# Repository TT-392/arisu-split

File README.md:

# Warning
For the actual arisu keyboard PCB go to https://github.com/FateNozomi/arisu-pcb, this one is just an unfinished fork.

# Arisu Keyboard PCB
アリス PCB designed using KiCad. The layout is inspired by Lyn's EM7 and TGR Alice with some modification of my own.

Key differences:
- I removed the extra [B] key on the right half and shifted the [NM,.?] row to the left by 0.25U.
- Shifted the 3 keys to the right and added arrow keys.
- Tweaked the bottom so that the 1.5U keys doesn't protrude out a little.

Shifting the [NM,.?] row to the left by 0.25U required quite some work on the arrangement of keys for the right half.
As a result, this does not give the same typing experience as Lyn's EM7 and TGR Alice.
Lyn's EM7 and TGR Alice uses the home row as the center point to vertically align both halves while I used the number row instead.
Due to the nature of staggered keyboards, aligning using the number row resulted in the home row not being aligned.

Disclaimer: Use these files at your own risk.

## Gerber Files
Download the gerber files under [releases](https://github.com/FateNozomi/arisu-pcb/releases).

## Assembly
For the components required, you may refer to the bill of materials included along with the release as reference or load up the design file in KiCad.
All the components can be soldered using a regular soldering iron, though soldering the Micro USB receptacle might be the biggest hurdle.

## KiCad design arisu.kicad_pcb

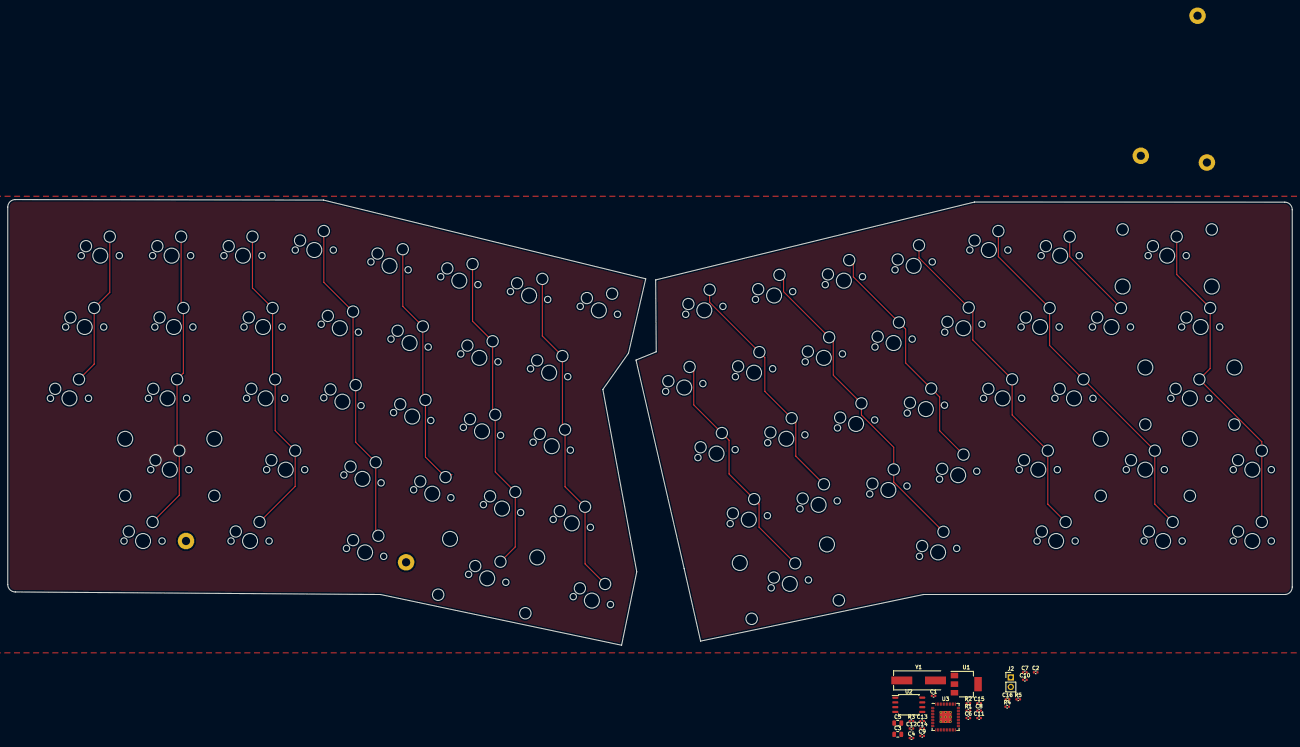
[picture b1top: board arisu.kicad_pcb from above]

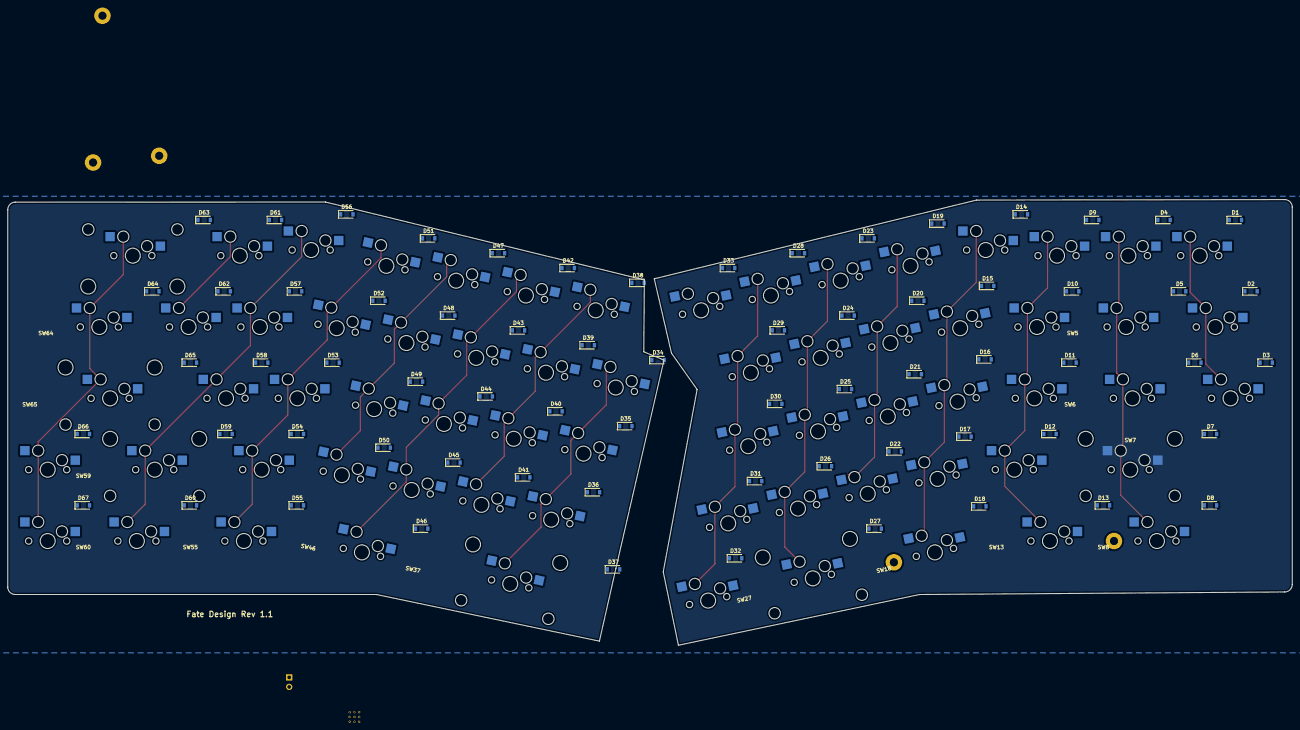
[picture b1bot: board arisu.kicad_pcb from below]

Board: 2 copper layers, 343.0 x 119.0 mm, 165 parts (67 on the bottom side), 108 nets.

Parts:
C1, C2: 27p; C_0402_1005Metric
C3, C5: 10u; C_0805_2012Metric
C4, C6, C7, C9, C11, C12, C13, C14, C15, C16: 100n; C_0402_1005Metric
C8, C10: 1u; C_0402_1005Metric
D1, D2, D3, D4, D5, D6, D7, D8, D9, D10, D11, D12, D13, D14, D15, D16, D17, D18, D19, D20, D21, D22, D23, D24, D25, D26, D27, D28, D29, D30, D31, D32, D33, D34, D35, D36, D37, D38, D39, D40, D41, D42, D43, D44, D45, D46, D47, D48, D49, D50, D51, D52, D53, D54, D55, D56, D57, D58, D59, D60, D61, D62, D63, D64, D65, D66, D67: D; D_SOD-123
H1, H2, H4, H6, H7: MountingHole; MountingHole_2.2mm_M2_Pad
J2: Conn_01x02; PinHeader_1x02_P2.54mm_Vertical
R1, R3: 1k; C_0402_1005Metric
R2: DNF; C_0402_1005Metric
R4, R5: 27; C_0402_1005Metric
SW1, SW2, SW3, SW4, SW9, SW10, SW11, SW12, SW14, SW15, SW16, SW17, SW19, SW20, SW21, SW22, SW23, SW24, SW25, SW26, SW28, SW29, SW30, SW31, SW32, SW33, SW34, SW35, SW36, SW38, SW39, SW40, SW41, SW42, SW43, SW44, SW45, SW47, SW48, SW49, SW50, SW51, SW52, SW53, SW54, SW56, SW57, SW58, SW61, SW62, SW66, SW67: SW_Push; SW_Cherry_MX_1.00u_PCB_Socket
SW5, SW8, SW13, SW18, SW46, SW55, SW60, SW64: SW_Push; SW_Cherry_MX_1.50u_PCB_Socket
SW6: SW_Push; SW_Cherry_MX_1.75u_PCB_Socket
SW7, SW65: SW_Push; SW_Cherry_MX_2.25u_PCB_Socket_ReversedStabilizers
SW27, SW59: SW_Push; SW_Cherry_MX_2.00u_PCB_Socket_ReversedStabilizers
SW37: SW_Push; SW_Cherry_MX_2.75u_PCB_Socket_ReversedStabilizers
SW63: SW_Push; SW_Cherry_MX_2.00u_PCB_Socket
U1: NCP1117-3.3_SOT223; SOT-223-3_TabPin2
U2: W25Q128JVS; SOIC-8_5.23x5.23mm_P1.27mm
U3: RP2040; RP2040-QFN-56
Y1: ABLS-12.000MHZ-B4-T; Crystal_SMD_HC49-US

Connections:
+3V3_L: C4.1, C5.1, C9.1, C10.1, C11.1, C12.1, C13.1, C14.1, C15.1, C16.1, R2.1, U1.2 (VO), U2.8 (VCC), U3.1 (IOVDD), U3.10 (IOVDD), U3.22 (IOVDD), U3.26 (RUN), U3.33 (IOVDD), U3.42 (IOVDD), U3.43 (ADC_AVDD), U3.44 (VREG_IN), U3.48 (USB_VDD), U3.49 (IOVDD)
+5R: C3.1, U1.3 (VI)
/Left/matrixL/col0: SW1.1, SW2.1, SW3.1
/Left/matrixL/col1: SW4.1, SW5.1, SW6.1, SW7.1, SW8.1
/Left/matrixL/col2: SW9.1, SW10.1, SW11.1, SW12.1, SW13.1
/Left/matrixL/col3: SW14.1, SW15.1, SW16.1, SW17.1, SW18.1
/Left/matrixL/col4: SW19.1, SW20.1, SW21.1, SW22.1, SW33.1
/Left/matrixL/col5: SW23.1, SW24.1, SW25.1, SW26.1, SW27.1
/Left/matrixL/col6: SW28.1, SW29.1, SW30.1, SW31.1, SW32.1
/Left/matrixL/row0: D1.1 (K), D4.1 (K), D9.1 (K), D14.1 (K), D19.1 (K), D23.1 (K), D28.1 (K)
/Left/matrixL/row1: D2.1 (K), D5.1 (K), D10.1 (K), D15.1 (K), D20.1 (K), D24.1 (K), D29.1 (K)
/Left/matrixL/row2: D3.1 (K), D6.1 (K), D11.1 (K), D16.1 (K), D21.1 (K), D25.1 (K), D30.1 (K)
/Left/matrixL/row3: D7.1 (K), D12.1 (K), D17.1 (K), D22.1 (K), D26.1 (K), D31.1 (K)
/Left/matrixL/row4: D8.1 (K), D13.1 (K), D18.1 (K), D27.1 (K), D32.1 (K), D33.1 (K)
/Right/1V1: C6.1, C7.1, C8.1, U3.23 (DVDD), U3.45 (VREG_VOUT), U3.50 (DVDD)
/Right/QSPI_SCLK: U2.6 (CLK), U3.52 (QSPI_SCLK)
/Right/QSPI_SD0: U2.5 (DI(IO0)), U3.53 (QSPI_SD0)
/Right/QSPI_SD1: U2.2 (DO(IO1)), U3.55 (QSPI_SD1)
/Right/QSPI_SD2: U2.3 (IO2), U3.54 (QSPI_SD2)
/Right/QSPI_SD3: U2.7 (IO3), U3.51 (QSPI_SD3)
/Right/QSPI_SS: R1.1, R2.2, U2.1 (~CS), U3.56 (QSPI_SS)
/Right/XIN: C1.1, U3.20 (XIN), Y1.1
/Right/XOUT: R3.1, U3.21 (XOUT)
/Right/matrixR/col0: SW34.1, SW35.1, SW36.1, SW37.1, U3.2 (GPIO0)
/Right/matrixR/col1: SW38.1, SW39.1, SW40.1, SW41.1, U3.3 (GPIO1)
/Right/matrixR/col2: SW42.1, SW43.1, SW44.1, SW45.1, SW46.1, U3.4 (GPIO2)
/Right/matrixR/col3: SW47.1, SW48.1, SW49.1, SW50.1, U3.5 (GPIO3)
/Right/matrixR/col4: SW51.1, SW52.1, SW53.1, SW54.1, SW55.1, U3.6 (GPIO4)
/Right/matrixR/col5: SW56.1, SW57.1, SW58.1, SW59.1, SW60.1, U3.7 (GPIO5)
/Right/matrixR/col6: SW61.1, SW62.1, U3.8 (GPIO6)
/Right/matrixR/col7: SW63.1, SW64.1, SW65.1, SW66.1, SW67.1, U3.9 (GPIO7)
/Right/matrixR/row0: D38.1 (K), D42.1 (K), D47.1 (K), D51.1 (K), D56.1 (K), D61.1 (K), D63.1 (K), U3.11 (GPIO8)
/Right/matrixR/row1: D34.1 (K), D39.1 (K), D43.1 (K), D48.1 (K), D52.1 (K), D57.1 (K), D62.1 (K), D64.1 (K), U3.12 (GPIO9)
/Right/matrixR/row2: D35.1 (K), D40.1 (K), D44.1 (K), D49.1 (K), D53.1 (K), D58.1 (K), D65.1 (K), U3.13 (GPIO10)
/Right/matrixR/row3: D36.1 (K), D41.1 (K), D45.1 (K), D50.1 (K), D54.1 (K), D59.1 (K), D66.1 (K), U3.14 (GPIO11)
/Right/matrixR/row4: D37.1 (K), D46.1 (K), D55.1 (K), D60.1 (K), D67.1 (K), U3.15 (GPIO12)
/Right/~USB_BOOT: J2.1, R1.2
GND: C1.2, C2.2, C3.2, C4.2, C5.2, C6.2, C7.2, C8.2, C9.2, C10.2, C11.2, C12.2, C13.2, C14.2, C15.2, C16.2, J2.2, U1.1 (GND), U2.4 (GND), U3.19 (TESTEN), U3.57 (GND)
unnamed: C2.1, R3.2, Y1.2
unnamed: D1.2 (A), SW1.2
unnamed: D2.2 (A), SW2.2
unnamed: D3.2 (A), SW3.2
unnamed: D4.2 (A), SW4.2
unnamed: D5.2 (A), SW5.2
unnamed: D6.2 (A), SW6.2
unnamed: D7.2 (A), SW7.2
unnamed: D8.2 (A), SW8.2
unnamed: D9.2 (A), SW9.2
unnamed: D10.2 (A), SW10.2
unnamed: D11.2 (A), SW11.2
unnamed: D12.2 (A), SW12.2
unnamed: D13.2 (A), SW13.2
unnamed: D14.2 (A), SW14.2
unnamed: D15.2 (A), SW15.2
unnamed: D16.2 (A), SW16.2
unnamed: D17.2 (A), SW17.2
unnamed: D18.2 (A), SW18.2
unnamed: D19.2 (A), SW19.2
unnamed: D20.2 (A), SW20.2
unnamed: D21.2 (A), SW21.2
unnamed: D22.2 (A), SW22.2
unnamed: D23.2 (A), SW23.2
unnamed: D24.2 (A), SW24.2
unnamed: D25.2 (A), SW25.2
unnamed: D26.2 (A), SW26.2
unnamed: D27.2 (A), SW27.2
unnamed: D28.2 (A), SW28.2
unnamed: D29.2 (A), SW29.2
unnamed: D30.2 (A), SW30.2
unnamed: D31.2 (A), SW31.2
unnamed: D32.2 (A), SW32.2
unnamed: D33.2 (A), SW33.2
unnamed: D34.2 (A), SW34.2
unnamed: D35.2 (A), SW35.2
unnamed: D36.2 (A), SW36.2
unnamed: D37.2 (A), SW37.2
unnamed: D38.2 (A), SW38.2
unnamed: D39.2 (A), SW39.2
unnamed: D40.2 (A), SW40.2
unnamed: D41.2 (A), SW41.2
unnamed: D42.2 (A), SW42.2
unnamed: D43.2 (A), SW43.2
unnamed: D44.2 (A), SW44.2
unnamed: D45.2 (A), SW45.2
unnamed: D46.2 (A), SW46.2
unnamed: D47.2 (A), SW47.2
unnamed: D48.2 (A), SW48.2
unnamed: D49.2 (A), SW49.2
unnamed: D50.2 (A), SW50.2
unnamed: D51.2 (A), SW51.2
unnamed: D52.2 (A), SW52.2
unnamed: D53.2 (A), SW53.2
unnamed: D54.2 (A), SW54.2
unnamed: D55.2 (A), SW55.2
unnamed: D56.2 (A), SW56.2
unnamed: D57.2 (A), SW57.2
unnamed: D58.2 (A), SW58.2
unnamed: D59.2 (A), SW59.2
unnamed: D60.2 (A), SW60.2
unnamed: D61.2 (A), SW61.2
unnamed: D62.2 (A), SW62.2
unnamed: D63.2 (A), SW63.2
unnamed: D64.2 (A), SW64.2
unnamed: D65.2 (A), SW65.2
unnamed: D66.2 (A), SW66.2
unnamed: D67.2 (A), SW67.2
unnamed: R4.2, U3.47 (USB_DP)
unnamed: R5.2, U3.46 (USB_DM)

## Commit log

2019-01-27 Move all footprints F.SilkS label to B.SilkS
2019-01-28 Add Buzzer_AST1109MLTRQ footprint
2019-01-28 Add Komi art footprint
2019-06-03 Organize parts
2019-06-04 Add HRO TYPE-C-31-M-12 footprint
2019-06-07 Add Kailh PCB Socket 1.00u and 2.00u footprint
2019-06-07 Add HRO TYPE-C-31-M-12 symbol library
2019-06-10 Define Kailh PCB Socket 1.00u and 2.00u courtyard
2019-07-25 Create LICENSE
2019-10-23 Add centered MX 1.00u, 2.00u, 6.25u and 7.00u footprints
2019-11-02 Remove Miscellaneous footprints
2019-11-02 Add SWD and I2C headers
2019-11-03 Add Fate logo
2020-10-20 Update .gitignore to include *.sch-bak
2020-10-20 Update symbol library to 5.1.7 USB_B_Micro USBLC6-25C6 ATmega32U4-AU
2020-10-20 Update MX_Switch footprints from Fate_Parts
2022-07-31 Convert to new kicad format
2022-07-31 Update 3d models
2022-07-31 Add Readme
2022-08-02 new layout
2022-08-03 scripting tests
2022-08-03 Added keycap models
2022-08-03 Convert stl files to step
2022-08-03 new commits in submodules
2022-08-03 Update remote of submodules
2022-08-04 Add RP2040
2022-08-04 Remove some more old files
2022-08-04 Split the keyboard into multiple files, give both sides a micro, and added 1 of the 2 jack circuits
2022-08-07 Hot pluggable trrs
2022-08-07 Added socketed versions of some keycaps, and center keycaps
2022-08-07 No more erc errors + centering and socketing of switches
2022-08-10 Add second micro back in, and added some footprints
2022-08-12 Schematic mostly finished
2022-08-12 Some layout
2022-08-17 Removed stabilizer holes from a footprint
2022-08-17 more layout, and some 3d files
2022-08-18 remove Fate_Parts submodule
2022-08-18 Remove the other 2 submodules
2022-08-20 Finished layout (for now), board outline, and new trrs jacks
2022-08-20 Moved some stuff´
2022-08-20 Moved footprints and 3d models into directories
2022-08-20 Move symbols into symbols folder
2022-08-22 Started work on e.eco case cutout
2022-08-24 Add cutout drawings
2022-10-17 plates added
2022-11-03 expand plate edges
2022-11-05 left side of keyboard finished for the time being
2022-11-08 Left side case created in blender
2022-11-08 temp commit, squash with next
2022-11-10 Fix left shift footprint, add stabilizer cutouts back in
2022-11-10 Make board outlines thin
2022-11-10 Left side gerbers generated
2022-11-10 move 3d file origin
2022-11-13 Add arisu logo and generate plate gerbers again
2022-11-13 Regenerate pcb_left gerbers
2022-12-13 replace usb right side, rotate micro, add protection diodes, trrs protection circuit mirrored, run pin cap removved, resistor footprints replaced
2022-12-22 temp commit merge with next
2023-01-01 Add back logo, improve layers for 3d model, remove silkscreen designators, basically fix right pcb
2023-01-01 Modify stabilizer holes, to comply with jlcpcb capability
2023-01-01 drc pass
2023-01-02 Update case blender files
2023-01-02 Add screw holes to case, and fix some stuff
2023-01-02 Case production files generated
2023-01-02 Generate remaining gerbers
